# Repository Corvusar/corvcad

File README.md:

<h1 align="center">CorvCAD</h1>

<p align="center">
  <strong>From the first wire to the box that holds it.</strong><br>
  A touch-first workspace for iPad that carries an electronic design from schematic, to circuit board, to enclosure.<br>
  A <a href="https://corvusar.com">Corvusar</a> project.
</p>

<table>
  <tr>
    <td width="50%"></td>
    <td width="50%"></td>
  </tr>
  <tr>
    <td align="center"><sub>Projects, tools and the Gerber viewer</sub></td>
    <td align="center"><sub>KiCad's own router, by touch (KiCad edition)</sub></td>
  </tr>
  <tr>
    <td></td>
    <td></td>
  </tr>
  <tr>
    <td align="center"><sub>Generated 3D parts on the board (FreeCAD edition)</sub></td>
    <td align="center"><sub>FreeCAD's feature timeline and clearance checks</sub></td>
  </tr>
</table>

## Contents

- [Scope](#scope)
- [Editions](#editions)
- [Features](#features)
- [Status](#status)
- [Getting started](#getting-started)
- [Repository layout](#repository-layout)
- [Documentation](#documentation)
- [Roadmap](#roadmap)
- [Contributing](#contributing)
- [Licensing](#licensing)
- [Trademarks](#trademarks)
- [Acknowledgements](#acknowledgements)

## Scope

A board is rarely the end of a design. It needs a schematic before it and a housing after it, and the two usually live in different programs on a desk. CorvCAD brings the whole path onto one iPad, in the formats engineers already use:

- **Electronics** in KiCad 10's own file format: `.kicad_pro`, `.kicad_sch`, `.kicad_pcb`. Projects open in desktop KiCad unchanged, and the reverse.
- **Mechanics** as an enclosure shaped around the board: a tray and lid, with cutouts, vents and screw posts. In the FreeCAD edition it is an editable FreeCAD document with exact solids.
- **Fabrication** from the same place: Gerbers and drill files for the board, STL, OBJ or STEP for the enclosure.

The portable C++ engine sits beneath a native SwiftUI and SceneKit app. Its C API is written so other front ends (macOS, Windows, Linux, Android) can follow; **none of them exists yet**.

CorvCAD is not a viewer, and not a remote desktop. In its native editions it compiles KiCad's and FreeCAD's own engines into the app. It is also not finished: see [Status](#status).

## Editions

One source tree builds three editions. Each adds to the one before it.

| Edition | Build flag | Licence | Adds |
|---|---|---|---|
| **Default** | none | MIT | CorvCAD's own engine: touch editing of KiCad projects, project libraries, a mesh enclosure, the Gerber viewer and the PCB calculator. |
| **KiCad** | `NATIVE_KICAD=YES` | GPL-3.0-or-later | KiCad 10.0.6's schematic and board engines, its libraries and its simulator. |
| **FreeCAD** | `NATIVE_FREECAD=YES` | GPL-3.0-or-later | FreeCAD 1.1.4's PartDesign enclosure, STEP, and generated 3D parts. |

Both flags together build one app with both engines.

## Features

### Electronics

| | Default | KiCad edition |
|---|:---:|:---:|
| Create, open and save KiCad 10 projects | ✓ | ✓ |
| Touch tools: parts, wires, labels, footprints, tracks, vias, zones, board outline, silkscreen and fab drawings | ✓ | ✓ |
| Hold menus: move, rotate, rename, delete, edit values and footprints; one undo history | ✓ | ✓ |
| Project symbol and footprint libraries, edited on a canvas | ✓ | ✓ |
| Update from schematic (pad nets) | ✓ | ✓ |
| KiCad's schematic model, hierarchy, buses, sheets, power rails, annotation | | ✓ |
| The official KiCad symbol and footprint libraries, with a part picker | | ✓ |
| KiCad's interactive router: walk around, shove, differential pairs, length and skew tuning | | ✓ |
| KiCad's DRC, ERC, zone fill, Board Setup and Update PCB from Schematic | | ✓ |
| Importers for Altium, Eagle, EasyEDA, CADSTAR, PADS, P-CAD, Fabmaster, LTspice and gEDA | | ✓ |
| SPICE simulation (ngspice), with **Electrify**: the board lit by its simulated voltages | | ✓ |
| Gerbers with job file, Excellon drill, placement, PDF/SVG plots, BOM and netlist | | ✓ |

### Mechanics

| | Default | FreeCAD edition |
|---|:---:|:---:|
| A tray and lid fitted to the board, with live 3D preview | ✓ | ✓ |
| STL and OBJ export | ✓ | ✓ |
| A FreeCAD PartDesign document, shown as its feature timeline | | ✓ |
| Connector cutouts, vent slot patterns, lid screw posts for screws or heat-set inserts | | ✓ |
| Sketch mode: rectangles, circles and polygons with arc edges, solved by FreeCAD's Sketcher, padded or pocketed | | ✓ |
| Mechanical-only projects, with no board | | ✓ |
| Components generated from their KiCad model names, and clearance checks against the lid and standoffs | placeholders | ✓ |
| Exact STEP and the editable `.FCStd` document | | ✓ |

### Everywhere

- **Gerber viewer**: RS-274X/X2 and Excellon, with layers stacked by function.
- **PCB calculator**: KiCad's own formulas for track width, vias, clearance, regulators and E-series values.
- **Fabricate**: board and enclosure specs, a material estimate, and every output the edition can write, in one place.

The full, screen-by-screen account is in the [feature reference](docs/FEATURES.md).

## Status

CorvCAD is pre-release software.

- **Tested on the iPad simulator.** Every edition has portrait and landscape UI tests. KiCad's outputs are compared with `kicad-cli` 10.0.6 on KiCad's own demo projects, and the 3D parts with KiCad's official models.
- **On a physical iPad Air (M2)**, the KiCad edition's netlists, ERC and DRC matched `kicad-cli` on four demo projects. The FreeCAD session's edits, history, saving and exports passed too. A full pass of every screen on a device is still open.
- **Unsigned builds only.** [Release v0.1.0](https://github.com/Corvusar/corvcad/releases/tag/v0.1.0) (2026-11-14) has the KiCad and FreeCAD editions' unsigned IPAs with their complete source; sign one yourself or build from source (below). No signed build is distributed.

## Getting started

### Requirements

- The engine: CMake 3.20+ and a C++20 compiler on macOS or Linux.
- The app: a Mac with Xcode (iOS 17 SDK or later) and [XcodeGen](https://github.com/yonaskolb/XcodeGen).

### Build and test the engine

```sh
cmake -S engine -B build/engine -DCMAKE_BUILD_TYPE=Release
cmake --build build/engine
ctest --test-dir build/engine --output-on-failure

# Try it: an enclosure from a board, and a schematic summary
build/engine/corvcad_cli engine/tests/fixtures/demo.kicad_pcb build/demo.stl
build/engine/corvcad_eda_cli inspect your-project.kicad_sch
```

With Open CASCADE installed, `-DCORVCAD_WITH_OCCT=ON` adds desktop STEP export: `corvcad_cli board.kicad_pcb enclosure.step --step`.

### Build the app (default edition)

```sh
xcodegen generate --spec app/project.yml
xcodebuild -project app/CorvCAD.xcodeproj -scheme CorvCAD \
  -sdk iphonesimulator -destination 'generic/platform=iOS Simulator' \
  CODE_SIGNING_ALLOWED=NO build
```

Or open `app/CorvCAD.xcodeproj` in Xcode and run it on a simulator, or on your own iPad with your own signing team. The UI tests (`-only-testing:CorvCADUITests`) capture every screen in both orientations.

### Build the KiCad and FreeCAD editions

The native editions compile KiCad, FreeCAD and their dependencies for iOS from pinned sources, which takes hours the first time. Follow:

- [KiCad core port](docs/KICAD_CORE_PORT.md): fetching KiCad 10.0.6, applying the patches, building the iOS dependencies and packaging.
- [FreeCAD iOS build](docs/history/FREECAD_F3_IOS_PORT.md): the static FreeCAD 1.1.4 package.
- [Combined workspace](docs/NATIVE_WORKSPACE.md): both engines in one app.

Then pass `NATIVE_KICAD=YES`, `NATIVE_FREECAD=YES` or both to `xcodebuild`.

### Install on an iPad

An unsigned IPA cannot be installed on an iPad as it is. Either build from source in Xcode with your own signing team, or sign the IPA yourself. [Releases](https://github.com/Corvusar/corvcad/releases) carry the KiCad and FreeCAD editions' unsigned IPAs, each beside the complete corresponding source for that build; the manual `release.yml` workflow makes them as a draft for a maintainer to publish. The manual `ci.yml` builds the default edition's `CorvCAD-unsigned.ipa`. [LiveContainer](https://github.com/LiveContainer/livecontainer.github.io/blob/main/docs/installation/standalone.md) with an AltStore or SideStore certificate is one route; CorvCAD does not need JIT.

## Repository layout

| Path | Contents |
|---|---|
| `engine/` | The portable C++20 engine and its C API (`include/corvcad/c_api.h`): KiCad file parsing and editing, geometry, STL, tests. |
| `app/` | The SwiftUI iPad app (generated with XcodeGen from `app/project.yml`) and its UI tests. |
| `integrations/kicad_core/` | The KiCad 10.0.6 port: pinned sources, patches, headless replacements, the native session and board code, ngspice, and the licence audit. |
| `integrations/freecad_core/` | The FreeCAD 1.1.4 port: pinned sources, patches, the iOS build, the mechanical session, and the licence audit. |
| `integrations/parts3d/` | The 3D part generator: KiCad's model generator ported to C++ on Open CASCADE. |
| `integrations/native_workspace/` | Both engines in one app over one shared dependency set. |
| `integrations/kicad_cli/`, `kicad_native/` | Desktop adapters that check CorvCAD's output with KiCad itself. |
| `docs/` | Architecture, features, port records and milestones. |
| `tools/` | Development helpers. |

## Documentation

- [Feature reference](docs/FEATURES.md): every screen and what it does.
- [Architecture](docs/ARCHITECTURE.md) and [milestones](docs/MILESTONES.md).
- [Touch editing](docs/TOUCH_EDITING.md) and the [schematic session API](docs/SCHEMATIC_SESSION_API.md).
- [KiCad integration](docs/KICAD_INTEGRATION.md), the [KiCad core port](docs/KICAD_CORE_PORT.md) and the [round-trip test project](docs/KICAD_TEST_PROJECT.md).
- [FreeCAD port](docs/FREECAD_PORT.md), [Open CASCADE on iOS](docs/OPEN_CASCADE_IOS.md) and the [combined workspace](docs/NATIVE_WORKSPACE.md).
- [3D models](docs/3D_MODELS.md) and the [simulator](docs/NGSPICE_PROPOSAL.md).
- Port records, kept as evidence: [KiCad gate 1](docs/history/KICAD_GATE1_HANDOFF.md), FreeCAD [F2](docs/history/FREECAD_F2_HANDOFF.md), [F3](docs/history/FREECAD_F3_HANDOFF.md), [F4](docs/history/FREECAD_F4_HANDOFF.md) and [F5 preparation](docs/history/FREECAD_F5_PREP.md).

## Roadmap

- A validation pass on physical iPads, including generated-part timing on large boards.
- Technical drawings, with PDF and DXF export.
- A slicer hand-off and G-code export.
- More 3D part families (SMD pin headers, QFN/DFN, SOT-223, TO, electrolytic capacitors), and typed heights for parts without a model.
- Boards with several outlines and internal slots.
- An accessibility pass.
- Front ends beyond iPad.

## Contributing

Contributions are welcome. Read [AGENTS.md](AGENTS.md) first: it holds the project's rules for code and for claims. In short:

- Keep `engine/` portable C++ with no Apple frameworks; UI lives in `app/`.
- Treat KiCad files as user data: preserve what an edit doesn't touch, and add a small fixture for parser changes.
- Describe what works precisely; mark anything unvalidated as such.
- A contribution takes the licence of the directory it lands in (see below).

## Licensing

CorvCAD's own code is [MIT](LICENSE). The native editions combine it with GPL code, so those apps are GPL-3.0-or-later as a whole.

| Path | Licence |
|---|---|
| Everything not listed below | MIT |
| `integrations/kicad_core/`: `patches/`, `headless/`, `session/kicad_*.cpp`, `probe/*.cpp` (KiCad-derived, linked with KiCad) | GPL-3.0-or-later |
| `integrations/freecad_core/patches/`, `integrations/freecad_core/ios/patches/` (changes to FreeCAD) | LGPL-2.1-or-later |
| `integrations/parts3d/` (port of kicad-packages3D-generator) | GPL-3.0-or-later |
| Retained upstream notices under `*/audit/` and `*-notices/` | their own licences |

| Built app | Licence | What a distributor must provide |
|---|---|---|
| Default edition | MIT | The MIT notice (on the Licences screen). |
| KiCad, FreeCAD or combined edition | GPL-3.0-or-later | The complete corresponding source for that build, including KiCad, FreeCAD and every dependency, plus all notices (on the Licences screen). |

Each file keeps its own notice; SPDX identifiers mark CorvCAD's files where the directory alone doesn't decide. [THIRD_PARTY.md](THIRD_PARTY.md) records every third-party component, its licence and its pinned version. KiCad's symbol and footprint libraries, bundled in the KiCad edition, are CC-BY-SA 4.0 with an exception that leaves designs made with them unrestricted.

## Trademarks

KiCad and FreeCAD are trademarks of their respective owners. CorvCAD is an independent project. It is not affiliated with, endorsed by or sponsored by the KiCad or FreeCAD projects, Open CASCADE SAS, or the ngspice developers. Their names are used only to describe what CorvCAD works with.

## Acknowledgements

Special thanks to the people behind these projects and libraries. CorvCAD wouldn't exist without them. It stands on their work, compiled in rather than imitated:

- [KiCad](https://www.kicad.org), its libraries, and its [3D model generator](https://gitlab.com/kicad/libraries/kicad-packages3D-generator)
- [FreeCAD](https://www.freecad.org) and [Open CASCADE Technology](https://dev.opencascade.org)
- [ngspice](https://ngspice.sourceforge.io)
- [wxWidgets](https://www.wxwidgets.org), [Boost](https://www.boost.org), [Python](https://www.python.org) and the other components listed in [THIRD_PARTY.md](THIRD_PARTY.md)

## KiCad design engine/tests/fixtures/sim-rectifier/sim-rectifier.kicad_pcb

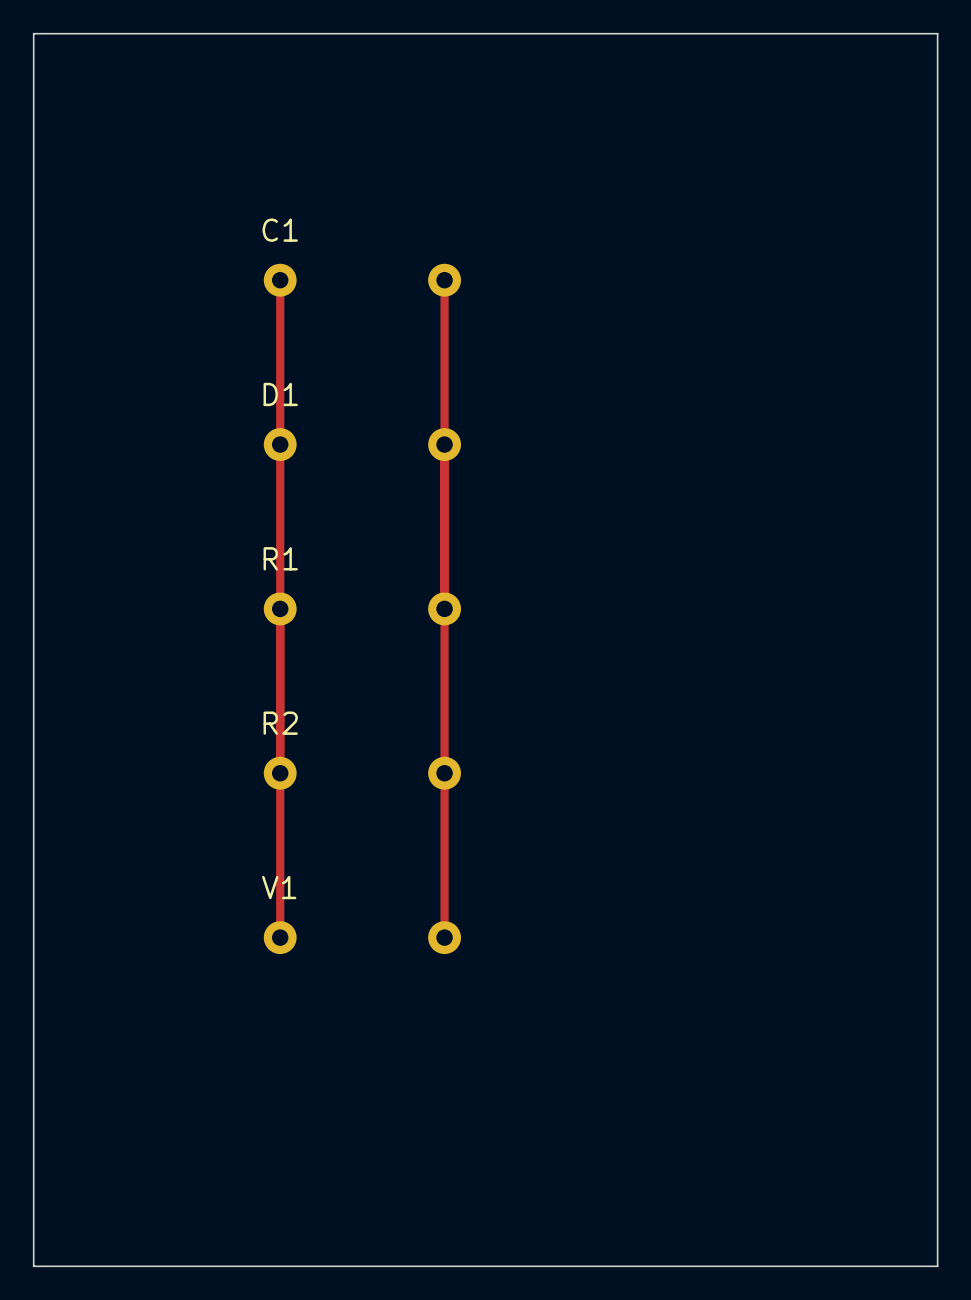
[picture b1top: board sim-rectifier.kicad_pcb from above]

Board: 0 copper layers, 55.0 x 75.0 mm, 5 parts (0 on the bottom side), 4 nets.

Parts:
C1: C1
D1: D1
R1: R1
R2: R2
V1: V1

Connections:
/rect_out: C1.1, D1.1, R2.1
/signal_in: R1.1, V1.1
GND: C1.2, R2.2, V1.2
unnamed: D1.2, R1.2

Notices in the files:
README.md:
Licence: MIT core, GPL-3.0-or-later native editions
